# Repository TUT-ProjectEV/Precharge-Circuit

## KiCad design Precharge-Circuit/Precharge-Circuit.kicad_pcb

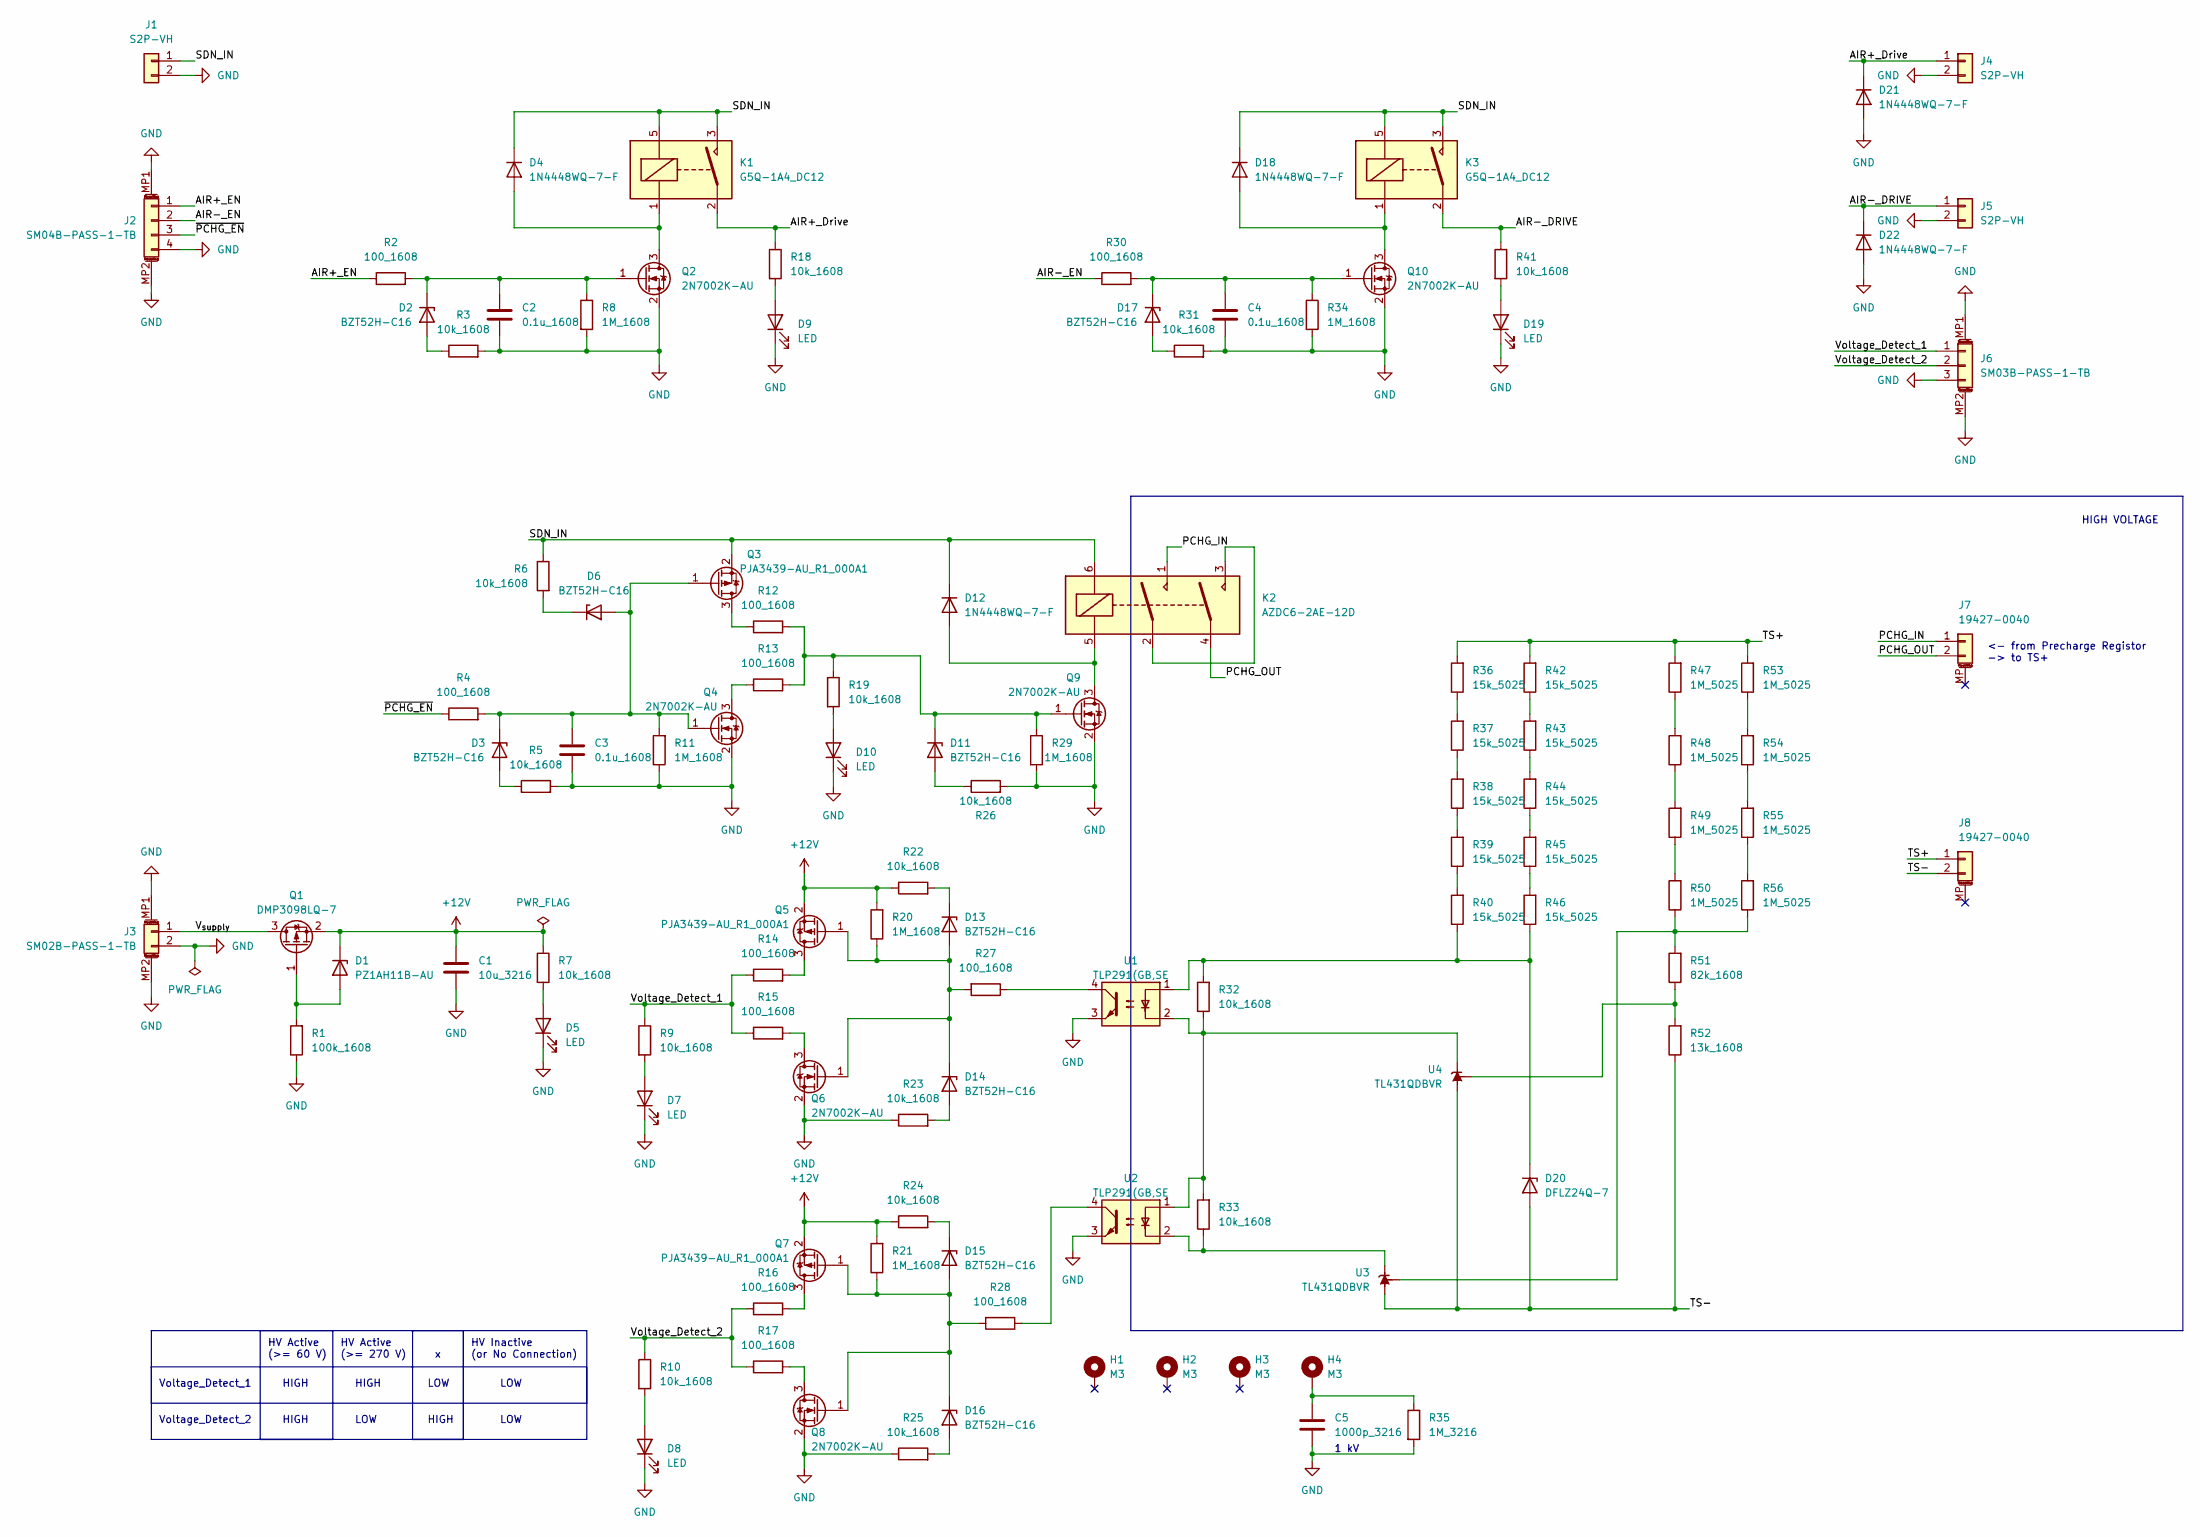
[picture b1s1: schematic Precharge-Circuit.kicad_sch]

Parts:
C1: 10u_3216; C_1206_3216Metric
C2, C3, C4: 0.1u_1608; C_0603_1608Metric
C5: 1000p_3216; C_1206_3216Metric
D1: PZ1AH11B-AU; D_SOD-123HE_PZ1AHxxxB-AU
D2, D3, D6, D11, D13, D14, D15, D16, D17: BZT52H-C16; D_SOD-123F_BZT52H-xxx
D4, D12, D18, D21, D22: 1N4448WQ-7-F; D_SOD-123_1N4448W
D5, D7, D8, D9, D10, D19: LED; LED_0603_1608Metric
D20: DFLZ24Q-7; D_PowerDI-123_DFLZxxQ
H1, H2, H3, H4: M3; MountingHole_3.2mm_M3_Pad_Via
J1, J4, J5: S2P-VH; Connector_S2P-VH
J2: SM04B-PASS-1-TB; Connector_SM04B-PASS-1-TB
J3: SM02B-PASS-1-TB; Connector_SM02B-PASS-1-TB
J6: SM03B-PASS-1-TB; Connector_SM03B-PASS-1-TB
J7, J8: 19427-0040; Connector_MX150L_19427-0040
K1, K3: G5Q-1A4_DC12; Relay_G5Q-1A4 DC12
K2: AZDC6-2AE-12D; Relay_AZDC6-2AE-12D
Q1: DMP3098LQ-7; Package_SOT-23_DMP3098LQ-7
Q2, Q4, Q6, Q8, Q9, Q10: 2N7002K-AU; Package_SOT-23_2N7002K-AU
Q3, Q5, Q7: PJA3439-AU_R1_000A1; Package_SOT-23_PJA3439-AU_R1_000A1
R1: 100k_1608; R_0603_1608Metric
R2, R4, R12, R13, R14, R15, R16, R17, R27, R28, R30: 100_1608; R_0603_1608Metric
R3, R5, R6, R7, R9, R10, R18, R19, R22, R23, R24, R25, R26, R31, R32, R33, R41: 10k_1608; R_0603_1608Metric
R8, R11, R20, R21, R29, R34: 1M_1608; R_0603_1608Metric
R35: 1M_3216; R_1206_3216Metric
R36, R37, R38, R39, R40, R42, R43, R44, R45, R46: 15k_5025; R_2010_5025Metric
R47, R48, R49, R50, R53, R54, R55, R56: 1M_5025; R_2010_5025Metric
R51: 82k_1608; R_0603_1608Metric
R52: 13k_1608; R_0603_1608Metric
U1, U2: TLP291(GB,SE; Isolator_TLP291(GB,SE
U3, U4: TL431QDBVR; Package_SOT-23-5_TL431QDBVR

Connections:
+12V: C1.1, D1.1 (K), Q1.2 (S), Q5.2 (S), Q7.2 (S), R7.1, R20.2, R21.2, R22.1, R24.1
/AIR+_Drive: D21.1 (K), J4.1, K1.2, R18.1
/AIR+_EN: J2.1, R2.1
/AIR-_DRIVE: D22.1 (K), J5.1, K3.2, R41.1
/AIR-_EN: J2.2, R30.1
/PCHG_IN: J7.1, K2.1
/PCHG_OUT: J7.2, K2.4
/SDN_IN: D4.1 (K), D12.1 (K), D18.1 (K), J1.1, K1.3, K1.5, K2.6, K3.3, K3.5, Q3.2 (S), R6.1
/TS+: J8.1, R36.2, R42.2, R47.2, R53.2
/TS-: D20.2 (A), J8.2, R52.1, U3.5 (A), U4.5 (A)
/V_{supply}: J3.1, Q1.3 (D)
/Voltage_Detect_1: J6.1, R9.1, R14.1, R15.1
/Voltage_Detect_2: J6.2, R10.1, R16.1, R17.1
/~PCHG_EN: J2.3, R4.1
GND: C1.2, C2.2, C3.2, C4.2, C5.2, D5.1 (K), D7.1 (K), D8.1 (K), D9.1 (K), D10.1 (K), D19.1 (K), D21.2 (A), D22.2 (A), J1.2, J2.4, J2.MP1 (MountPin), J2.MP2 (MountPin), J3.2, J3.MP1 (MountPin), J3.MP2 (MountPin), J4.2, J5.2, J6.3, J6.MP1 (MountPin), J6.MP2 (MountPin), Q2.2 (S), Q4.2 (S), Q6.2 (S), Q8.2 (S), Q9.2 (S), Q10.2 (S), R1.1, R3.2, R5.2, R8.2, R11.1, R23.1, R25.1, R26.2, R29.2, R31.2, R34.2, R35.2, U1.3 (Emitter), U2.3 (Emitter)
unnamed: C5.1, H4.1, R35.1
unnamed: D1.2 (A), Q1.1 (G), R1.2
unnamed: D2.2 (A), R3.1
unnamed: C2.1, D2.1 (K), Q2.1 (G), R2.2, R8.1
unnamed: D3.2 (A), R5.1
unnamed: C3.1, D3.1 (K), D6.2 (A), Q3.1 (G), Q4.1 (G), R4.2, R11.2
unnamed: D4.2 (A), K1.1, Q2.3 (D)
unnamed: D5.2 (A), R7.2
unnamed: D6.1 (K), R6.2
unnamed: D7.2 (A), R9.2
unnamed: D8.2 (A), R10.2
unnamed: D9.2 (A), R18.2
unnamed: D10.2 (A), R19.2
unnamed: D11.2 (A), R26.1
unnamed: D11.1 (K), Q9.1 (G), R12.2, R13.2, R19.1, R29.1
unnamed: D12.2 (A), K2.5, Q9.3 (D)
unnamed: D13.2 (A), D14.1 (K), Q5.1 (G), Q6.1 (G), R20.1, R27.2
unnamed: D13.1 (K), R22.2
unnamed: D14.2 (A), R23.2
unnamed: D15.2 (A), D16.1 (K), Q7.1 (G), Q8.1 (G), R21.1, R28.2
unnamed: D15.1 (K), R24.2
unnamed: D16.2 (A), R25.2
unnamed: D17.2 (A), R31.1
unnamed: C4.1, D17.1 (K), Q10.1 (G), R30.2, R34.1
unnamed: D18.2 (A), K3.1, Q10.3 (D)
unnamed: D19.2 (A), R41.2
unnamed: D20.1 (K), R32.2, R40.1, R46.1, U1.1 (Anode)
unnamed: K2.2, K2.3
unnamed: Q3.3 (D), R12.1
unnamed: Q4.3 (D), R13.1
unnamed: Q5.3 (D), R14.2
unnamed: Q6.3 (D), R15.2
unnamed: Q7.3 (D), R16.2
unnamed: Q8.3 (D), R17.2
unnamed: R36.1, R37.2
unnamed: R37.1, R38.2
unnamed: R38.1, R39.2
unnamed: R39.1, R40.2
unnamed: R42.1, R43.2
unnamed: R43.1, R44.2
unnamed: R44.1, R45.2
unnamed: R45.1, R46.2
unnamed: R47.1, R48.2
unnamed: R48.1, R49.2
unnamed: R49.1, R50.2
unnamed: R53.1, R54.2
unnamed: R54.1, R55.2
unnamed: R55.1, R56.2
unnamed: R32.1, R33.2, U1.2 (Cathode), U2.1 (Anode), U4.3 (K)
unnamed: R27.1, U1.4 (Collector)
unnamed: R33.1, U2.2 (Cathode), U3.3 (K)
unnamed: R28.1, U2.4 (Collector)
unnamed: R50.1, R51.2, R56.1, U3.4 (REF)
unnamed: R51.1, R52.2, U4.4 (REF)

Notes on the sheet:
HIGH
HIGH VOLTAGE
LOW
HV Inactive (or No Connection)
<- from Precharge Registor -> to TS+
HV Active (>= 270 V)
Voltage_Detect_1
HV Active (>= 60 V)
Voltage_Detect_2
1 kV

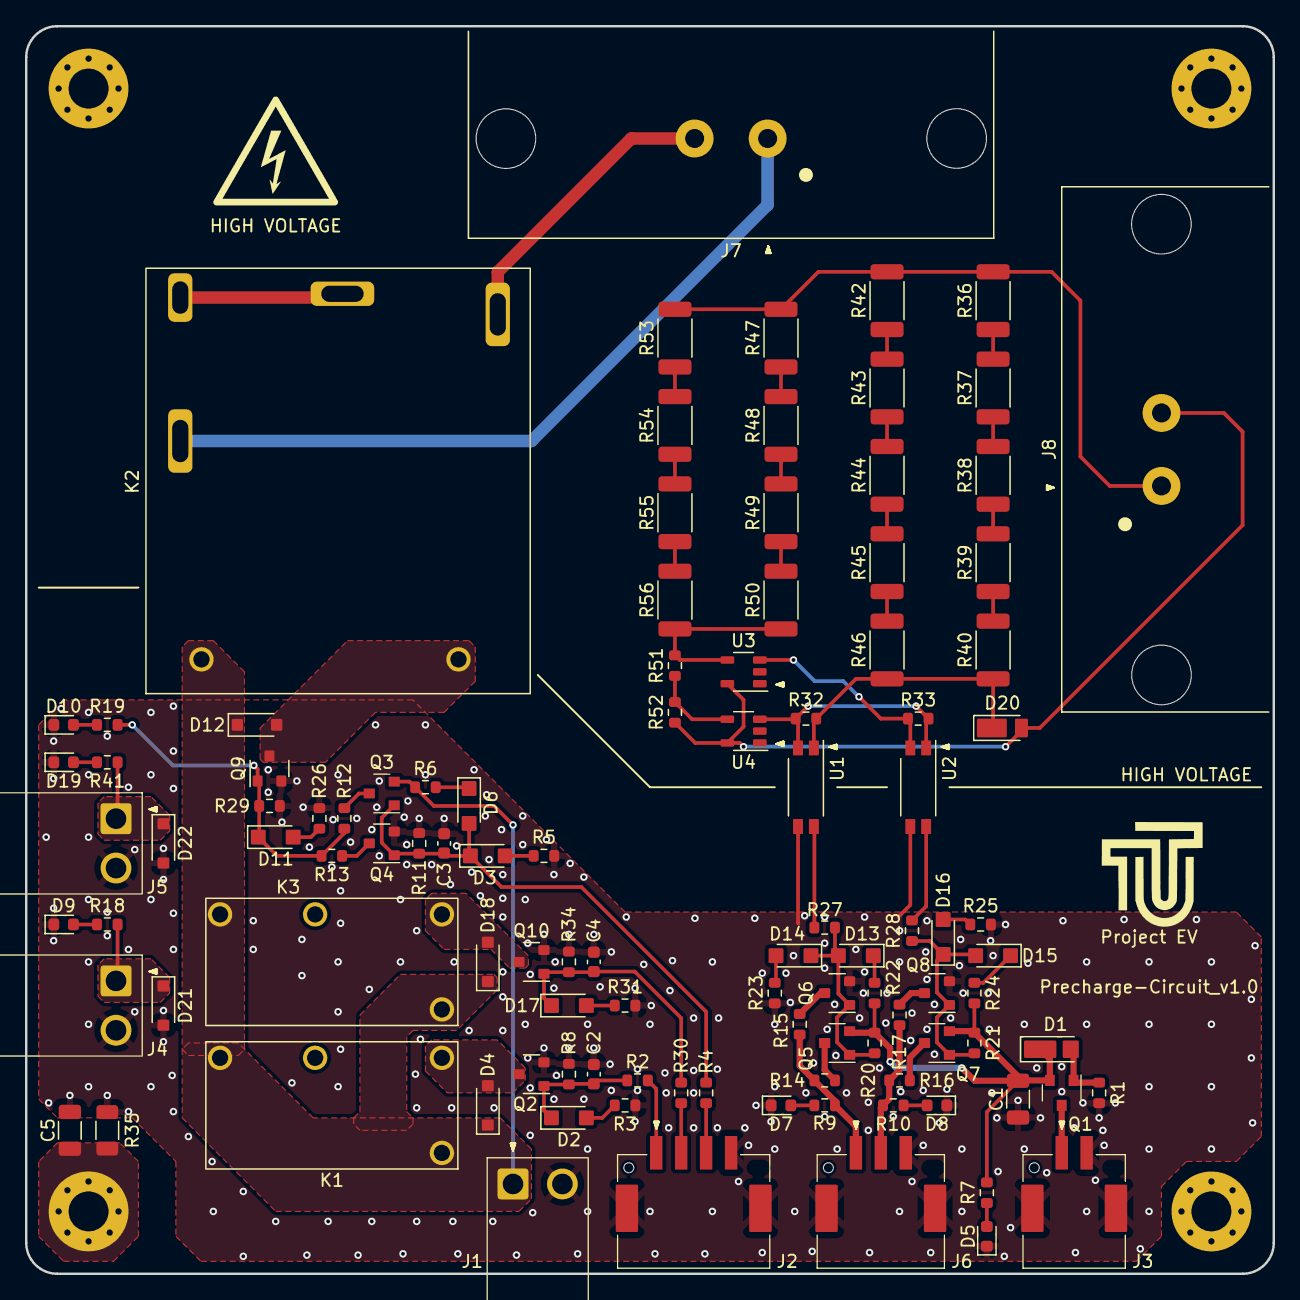
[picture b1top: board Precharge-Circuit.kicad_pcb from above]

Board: 2 copper layers, 100.0 x 100.0 mm, 112 parts (0 on the bottom side), 69 nets.

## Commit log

2024-03-17 Initialize main
2024-03-17 create project
    AIRドライブ回路、プリチャージ回路まで作成
    定数未決定
2024-03-17 add ignore folder
    Precharge-Circuit-backups
2024-03-19 用紙サイズ変更
2024-03-19 電圧検知追加
2024-03-19 12V電源入力追加
2024-03-19 電圧検知信号ライン修正
2024-03-20 電圧検知信号のインジケータと出力をMOSFET駆動に変更
2024-03-23 コネクタ修正、信号出力をプッシュプルに修正
2024-03-23 アノテーションし直し
2024-03-23 フットプリント割当、ERCOK
2024-03-24 シンボル更新
2024-03-24 フットプリント追加
2024-03-24 位置修正、ツェナーの電流制限抵抗追加
2024-03-24 パーツ配置、ピンアサイン変更
2024-03-25 パーツ配置
2024-03-27 NOT ゲートの電流制限抵抗追加、高電圧コネクタフットプリント更新、配線GNDベタ以外
2024-03-27 配線完了、DRC実行エラーなし・警告あり
2024-03-27 完成、配線修正、シルク位置修正、シルク追加
